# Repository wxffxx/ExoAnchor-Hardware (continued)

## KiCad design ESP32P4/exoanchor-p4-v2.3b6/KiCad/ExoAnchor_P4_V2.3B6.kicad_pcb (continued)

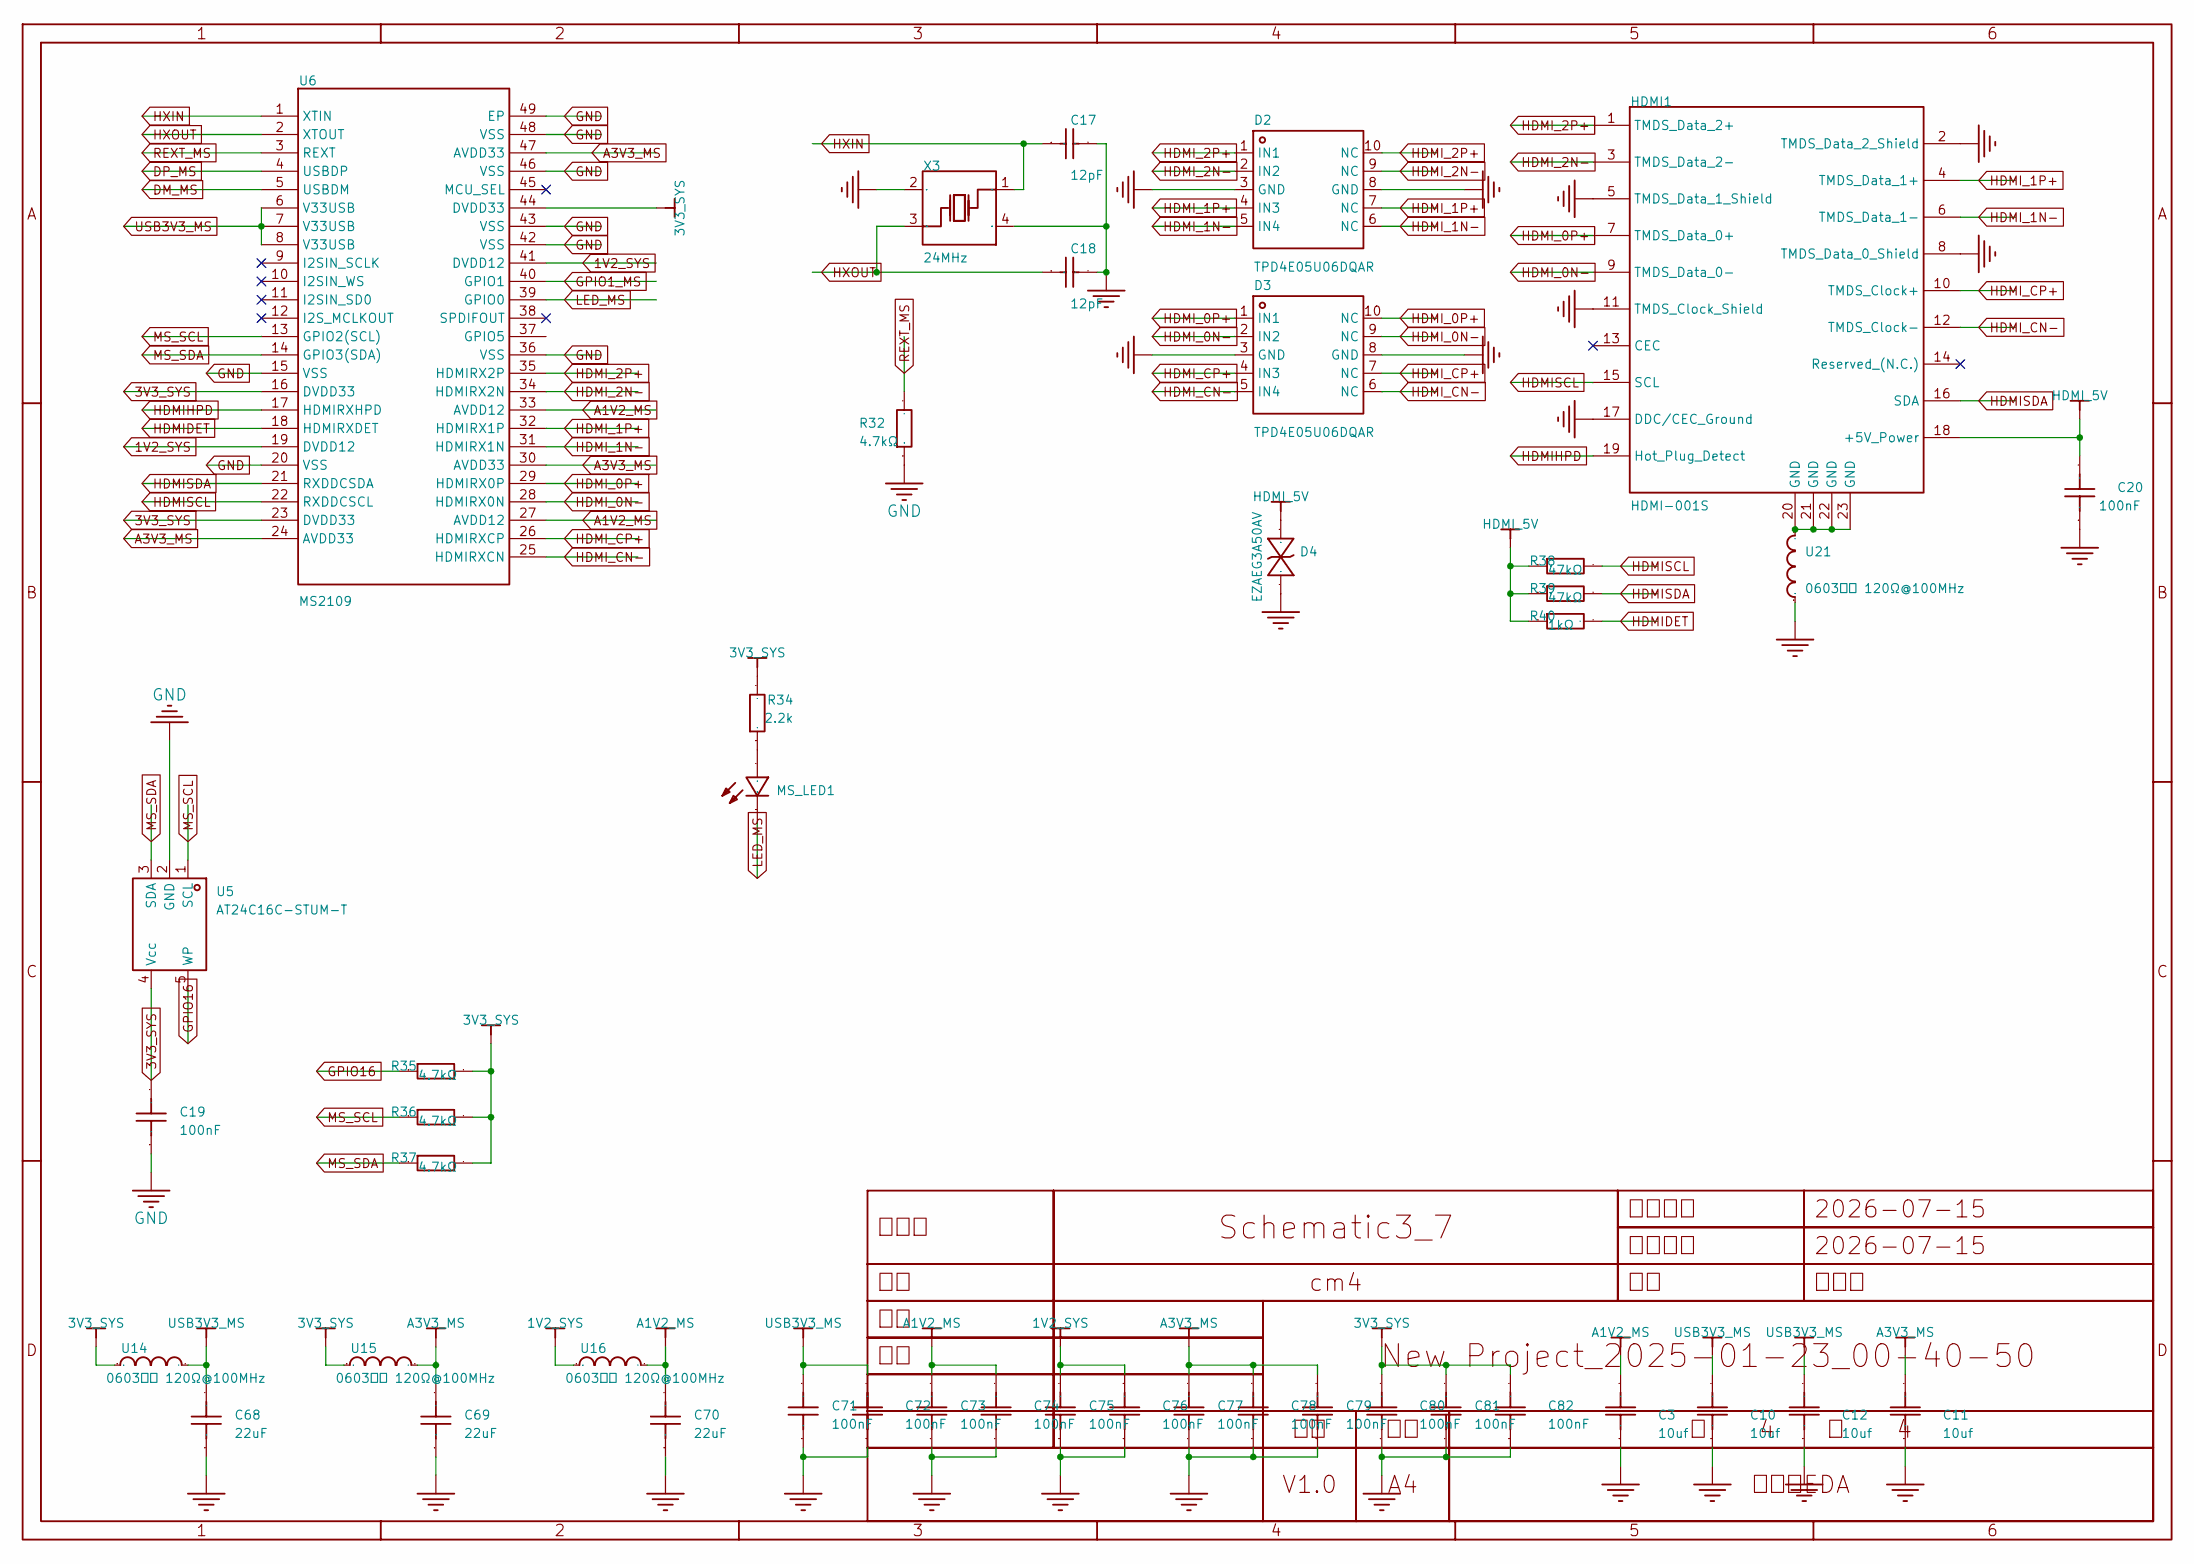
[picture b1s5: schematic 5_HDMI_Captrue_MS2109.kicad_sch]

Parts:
C3, C10, C11, C12: 10uf; C0603__a4480e4e; Tolerance ±10%; Voltage Rated 50V; Manufacturer Part CL10A105KB8NNNC; LCSC Part Name 1uF ±10% 50V
C17, C18: 12pF; C0402__aba8f707; Tolerance ±5%; Voltage Rating 50V; Manufacturer Part 0402CG120J500NT; LCSC Part Name 12pF ±5% 50V
C19, C20: 100nF; C0603__62af29ea; Tolerance ±10%; Voltage Rated 50V; Manufacturer Part CC0603KRX7R9BB104; LCSC Part Name 100nF ±10% 50V
C68, C69, C70: 22uF; C0805__eb27e37a; Tolerance ±20%; Voltage Rating 25V; Manufacturer Part CGA0805X5R226M250MT; LCSC Part Name 22uF ±20% 25V
C71, C72, C73, C74, C75, C76, C77, C78, C79, C80, C81, C82: 100nF; C0402 去耦电容__92f207f8; Tolerance ±10%; Voltage Rating 16V; Manufacturer Part CL05B104KO5NNNC; LCSC Part Name 100nF ±10% 16V
D2, D3: TPD4E05U06DQAR; USON-10_L2.5-W1.0-P0.50-BL__5b0cdc5b; Manufacturer Part TPD4E05U06DQAR; LCSC Part Name 单向ESD
D4: EZAEG3A50AV; D0603-BI__29d920bd; Manufacturer Part EZAEG3A50AV; LCSC Part Name EZAEG3A50AV
HDMI1: HDMI-001S; HDMI-SMD_HDMI-001S__cd4ec1f9; Manufacturer Part HDMI-001S; LCSC Part Name HDMI-001S
MS_LED1: LED0603-RD_RED__01c91157; Manufacturer Part NCD0603R1; LCSC Part Name NCD0603R1
R32: 4.7kΩ; R0402__b4a31b25; Tolerance ±1%; Voltage-Supply(Max) 50V; Manufacturer Part RC0402FR-074K7L; LCSC Part Name 厚膜电阻 4.7kΩ ±1% 62.5mW
R34: 2.2k; R0603__52b39882; Overload Voltage (Max) 75V; Tolerance ±1%; Manufacturer Part 0603WAF1001T5E; LCSC Part Name 1kΩ ±1% 100mW 厚膜电阻
R35, R36, R37: 4.7kΩ; R0603__601aad73; Tolerance ±1%; Manufacturer Part 0603WAF4701T5E; LCSC Part Name 4.7kΩ ±1% 100mW 厚膜电阻
R38, R39: 47kΩ; R0603__601aad73; Overload Voltage (Max) 75V; Tolerance ±1%; Manufacturer Part 0603WAF4701T5E; LCSC Part Name 4.7kΩ ±1% 100mW 厚膜电阻
R40: 1kΩ; R0603__52b39882; Overload Voltage (Max) 75V; Tolerance ±1%; Manufacturer Part 0603WAF1001T5E; LCSC Part Name 1kΩ ±1% 100mW 厚膜电阻
U5: AT24C16C-STUM-T; SOT-23-5_L2.9-W1.6-P0.95-LS2.8-BL__13f3e689; Manufacturer Part AT24C16C-STUM-T; LCSC Part Name 兼容I²C（两线制）的16 Kbit串行EEPROM
U6: MS2109; QFN-48_L7.0-W7.0-P0.50-TL-EP4.1__b8ae6dac
U14: L0603__0fd5099d; Manufacturer Part BLM18PG121SN1D; LCSC Part Name 0603磁珠 120Ω@100MHz
U15, U16, U21: BLM18PG121SN1D; L0603__0fd5099d; Current Rating 2A; Tolerance ±25%; Manufacturer Part BLM18PG121SN1D; LCSC Part Name 0603磁珠 120Ω@100MHz
X3: 24MHz; CRYSTAL-SMD_4P-L3.2-W2.5-BL__9c9dbee8; Manufacturer Part X322524MOB4SI; LCSC Part Name YSX321SL 24MHZ 4P 3225 12PF ±10PPM -40~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

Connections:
1V2_SYS: C75.2, C76.2, U6.19 (DVDD12), U6.41 (DVDD12), U16.1; also elsewhere on the board
3V3_SYS: C19.2, C80.2, C81.2, C82.2, R34.2, R35.2, R36.2, R37.2, U5.4 (Vcc), U6.16 (DVDD33), U6.23 (DVDD33), U6.44 (DVDD33), U14.1, U15.1; also elsewhere on the board
$5N3531: MS_LED1.2 (A), R34.1
$5N70958: HDMI1.20 (GND), HDMI1.21 (GND), HDMI1.22 (GND), HDMI1.23 (GND), U21.2
A1V2_MS: C3.2, C70.2, C73.2, C74.2, U6.27 (AVDD12), U6.33 (AVDD12), U16.2
A3V3_MS: C11.2, C69.2, C77.2, C78.2, C79.2, U6.24 (AVDD33), U6.30 (AVDD33), U6.47 (AVDD33), U15.2
DM_MS: U6.5 (USBDM); also elsewhere on the board
DP_MS: U6.4 (USBDP); also elsewhere on the board
GND: C3.1, C10.1, C11.1, C12.1, C17.2, C18.2, C19.1, C20.1, C68.1, C69.1, C70.1, C71.1, C72.1, C73.1, C74.1, C75.1, C76.1, C77.1, C78.1, C79.1, C80.1, C81.1, C82.1, D2.3 (GND), D2.8 (GND), D3.3 (GND), D3.8 (GND), D4.1 (K), HDMI1.2 (TMDS_Data_2_Shield), HDMI1.5 (TMDS_Data_1_Shield), HDMI1.8 (TMDS_Data_0_Shield), HDMI1.11 (TMDS_Clock_Shield), HDMI1.17 (DDC/CEC_Ground), R32.1, U5.2 (GND), U6.15 (VSS), U6.20 (VSS), U6.36 (VSS), U6.42 (VSS), U6.43 (VSS), U6.46 (VSS), U6.48 (VSS), U6.49 (EP), U21.1, X3.2 (GND), X3.4 (GND); also elsewhere on the board
GPIO1_MS: U6.40 (GPIO1)
GPIO16: R35.1, U5.5 (WP); also elsewhere on the board
HDMIDET: R40.2, U6.18 (HDMIRXDET)
HDMIHPD: HDMI1.19 (Hot_Plug_Detect), U6.17 (HDMIRXHPD)
HDMISCL: HDMI1.15 (SCL), R38.2, U6.22 (RXDDCSCL)
HDMISDA: HDMI1.16 (SDA), R39.2, U6.21 (RXDDCSDA)
HDMI_0N-: D3.2 (IN2), D3.9 (NC), HDMI1.9 (TMDS_Data_0-), U6.28 (HDMIRX0N)
HDMI_0P+: D3.1 (IN1), D3.10 (NC), HDMI1.7 (TMDS_Data_0+), U6.29 (HDMIRX0P)
HDMI_1N-: D2.5 (IN4), D2.6 (NC), HDMI1.6 (TMDS_Data_1-), U6.31 (HDMIRX1N)
HDMI_1P+: D2.4 (IN3), D2.7 (NC), HDMI1.4 (TMDS_Data_1+), U6.32 (HDMIRX1P)
HDMI_2N-: D2.2 (IN2), D2.9 (NC), HDMI1.3 (TMDS_Data_2-), U6.34 (HDMIRX2N)
HDMI_2P+: D2.1 (IN1), D2.10 (NC), HDMI1.1 (TMDS_Data_2+), U6.35 (HDMIRX2P)
HDMI_5V: C20.2, D4.2 (A), HDMI1.18 (+5V_Power), R38.1, R39.1, R40.1
HDMI_CN-: D3.5 (IN4), D3.6 (NC), HDMI1.12 (TMDS_Clock-), U6.25 (HDMIRXCN)
HDMI_CP+: D3.4 (IN3), D3.7 (NC), HDMI1.10 (TMDS_Clock+), U6.26 (HDMIRXCP)
HXIN: C17.1, U6.1 (XTIN), X3.1 (OSC1)
HXOUT: C18.1, U6.2 (XTOUT), X3.3 (OSC2)
LED_MS: MS_LED1.1 (K), U6.39 (GPIO0)
MS_SCL: R36.1, U5.1 (SCL), U6.13 (GPIO2(SCL)); also elsewhere on the board
MS_SDA: R37.1, U5.3 (SDA), U6.14 (GPIO3(SDA)); also elsewhere on the board
REXT_MS: R32.2, U6.3 (REXT)
USB3V3_MS: C10.2, C12.2, C68.2, C71.2, C72.2, U6.6 (V33USB), U6.7 (V33USB), U6.8 (V33USB), U14.2

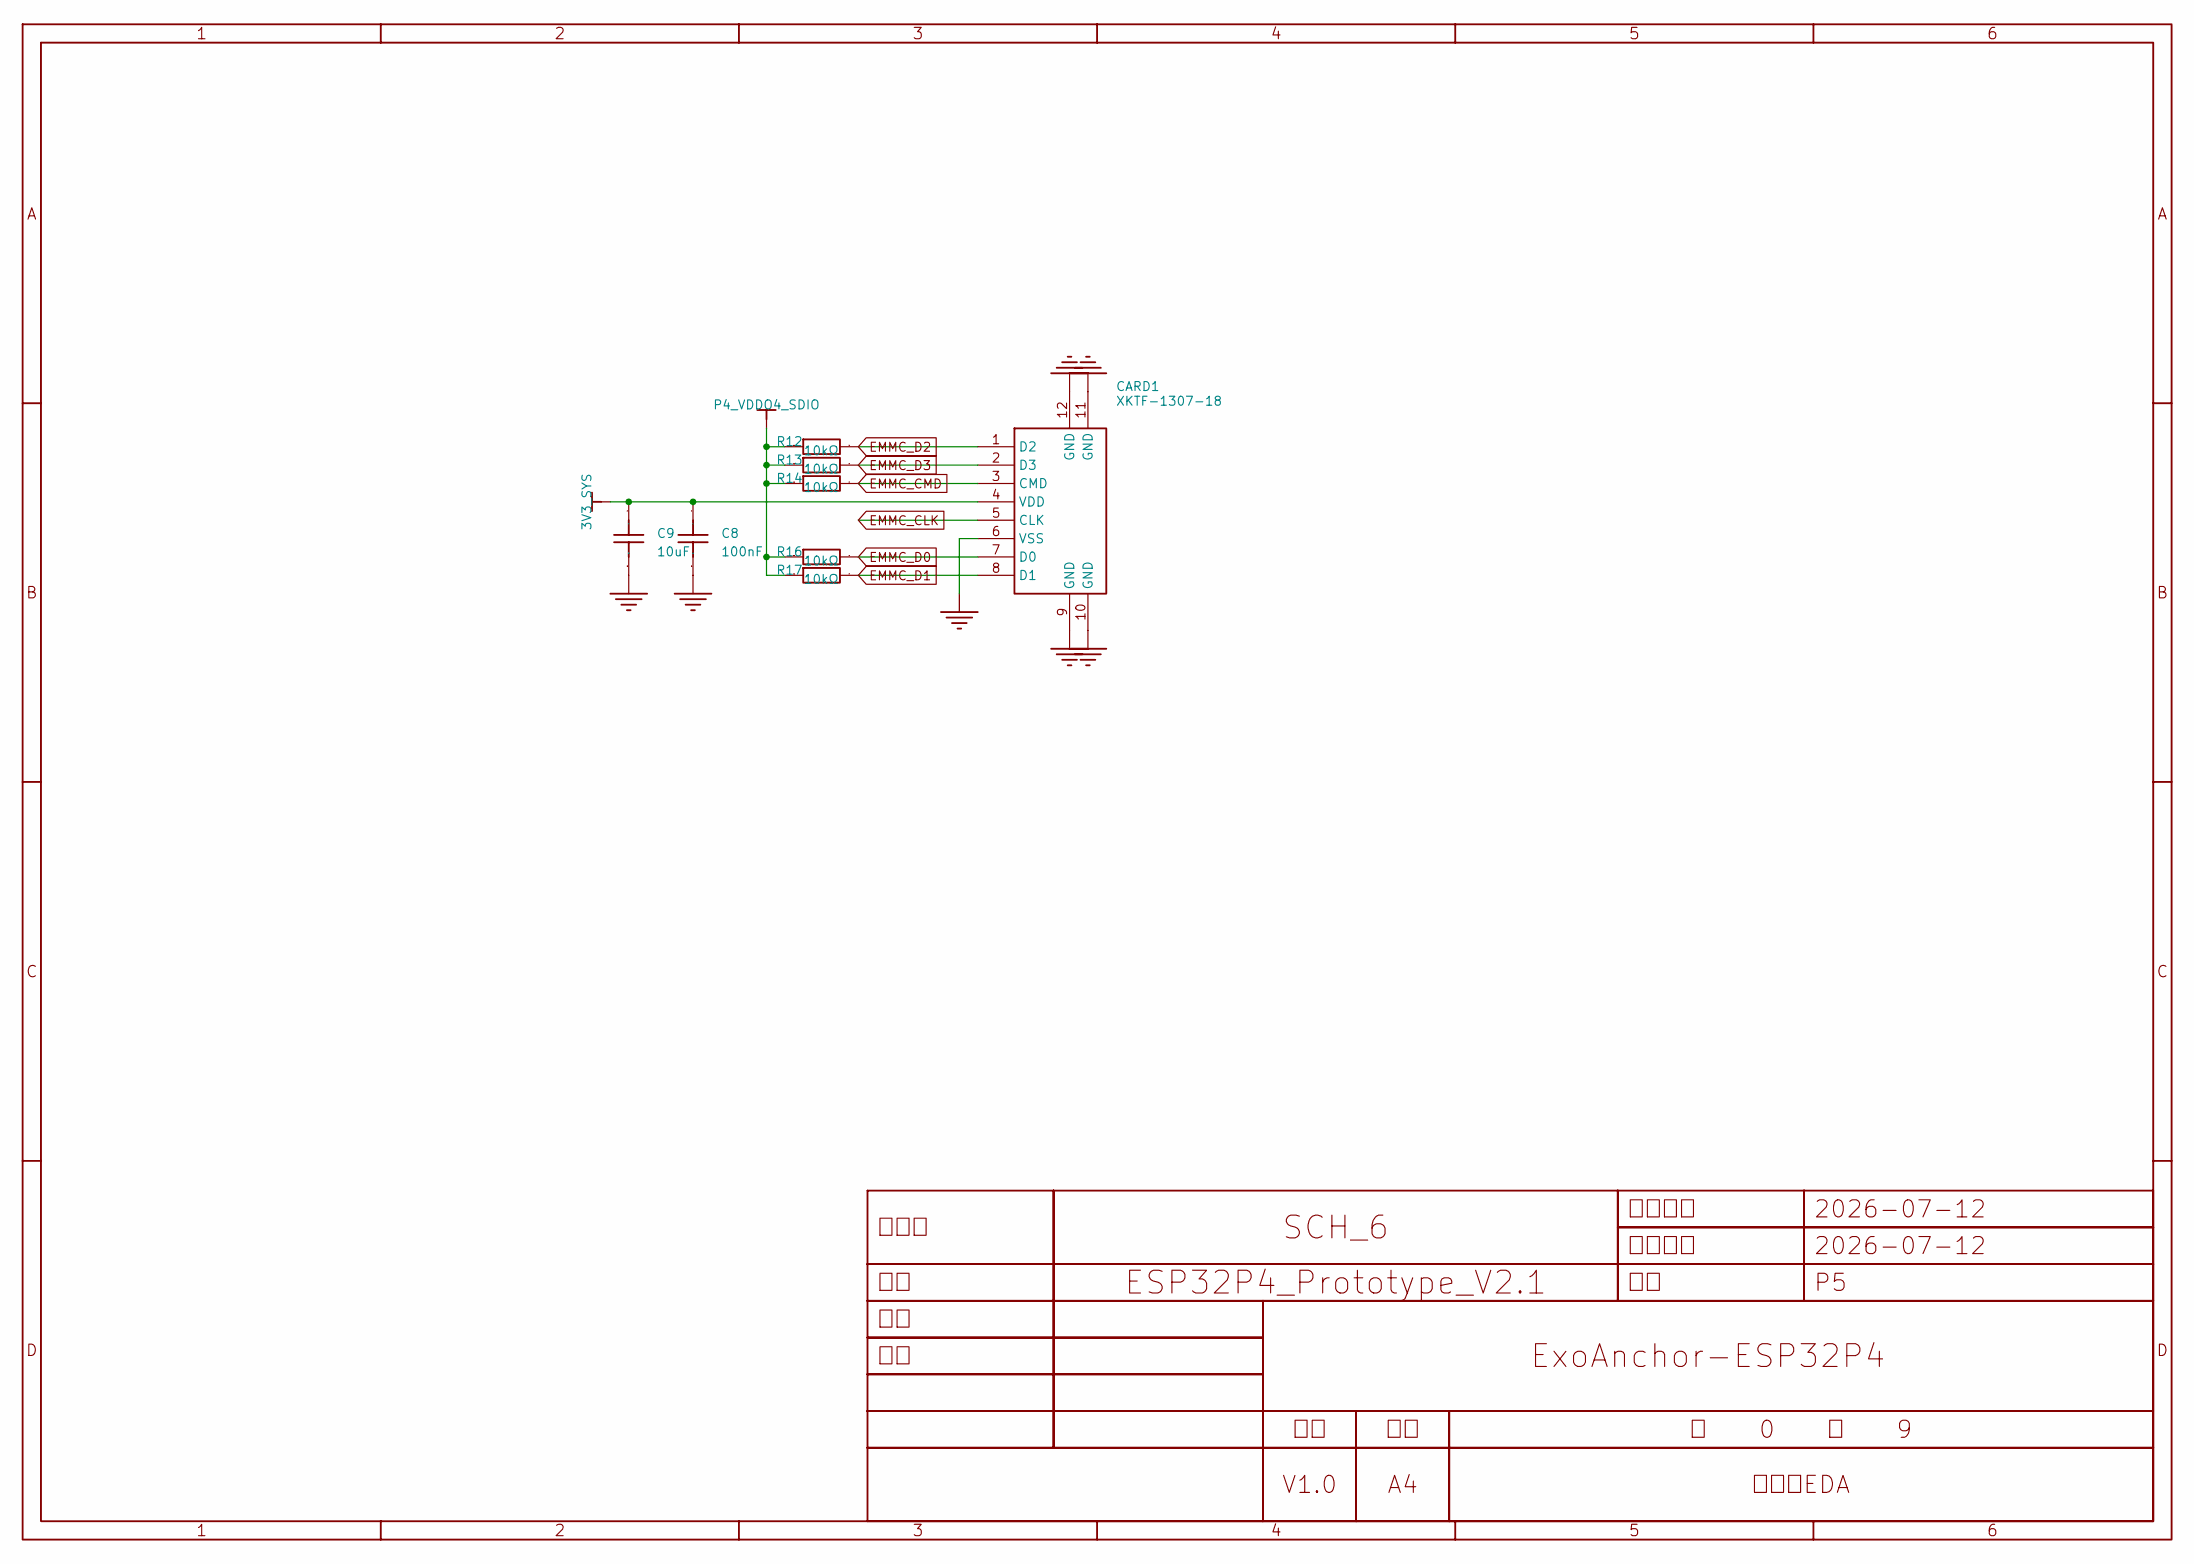
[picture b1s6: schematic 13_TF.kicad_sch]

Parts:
C8: 100nF; C0603__a4480e4e; Tolerance ±10%; Voltage Rating 16V; Manufacturer Part CL05B104KO5NNNC; LCSC Part Name 100nF ±10% 16V
C9: 10uF; C0603__a4480e4e; Tolerance ±20%; Voltage Rating 16V; Manufacturer Part CGA0603X5R106M160JT; LCSC Part Name 10uF ±20% 16V
CARD1: XKTF-1307-18; TF-SMD_XKTF-1307-18__7bd28ea8; Manufacturer Part XKTF-1307-18; LCSC Part Name 翻盖式 MicroSD卡(TF卡) 卡座
R12, R13, R14, R16, R17: 10kΩ; R0603__0f1821c5; Manufacturer Part FRC0402F1002TS; LCSC Part Name 10kΩ ±1% 62.5mW 厚膜电阻

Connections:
3V3_SYS: C8.2, C9.2, CARD1.4 (VDD); also elsewhere on the board
EMMC_CLK: CARD1.5 (CLK); also elsewhere on the board
EMMC_CMD: CARD1.3 (CMD), R14.2; also elsewhere on the board
EMMC_D0: CARD1.7 (D0), R16.2; also elsewhere on the board
EMMC_D1: CARD1.8 (D1), R17.2; also elsewhere on the board
EMMC_D2: CARD1.1 (D2), R12.2; also elsewhere on the board
EMMC_D3: CARD1.2 (D3), R13.2; also elsewhere on the board
GND: C8.1, C9.1, CARD1.6 (VSS), CARD1.9 (GND), CARD1.10 (GND), CARD1.11 (GND), CARD1.12 (GND); also elsewhere on the board
P4_VDDO4_SDIO: R12.1, R13.1, R14.1, R16.1, R17.1; also elsewhere on the board

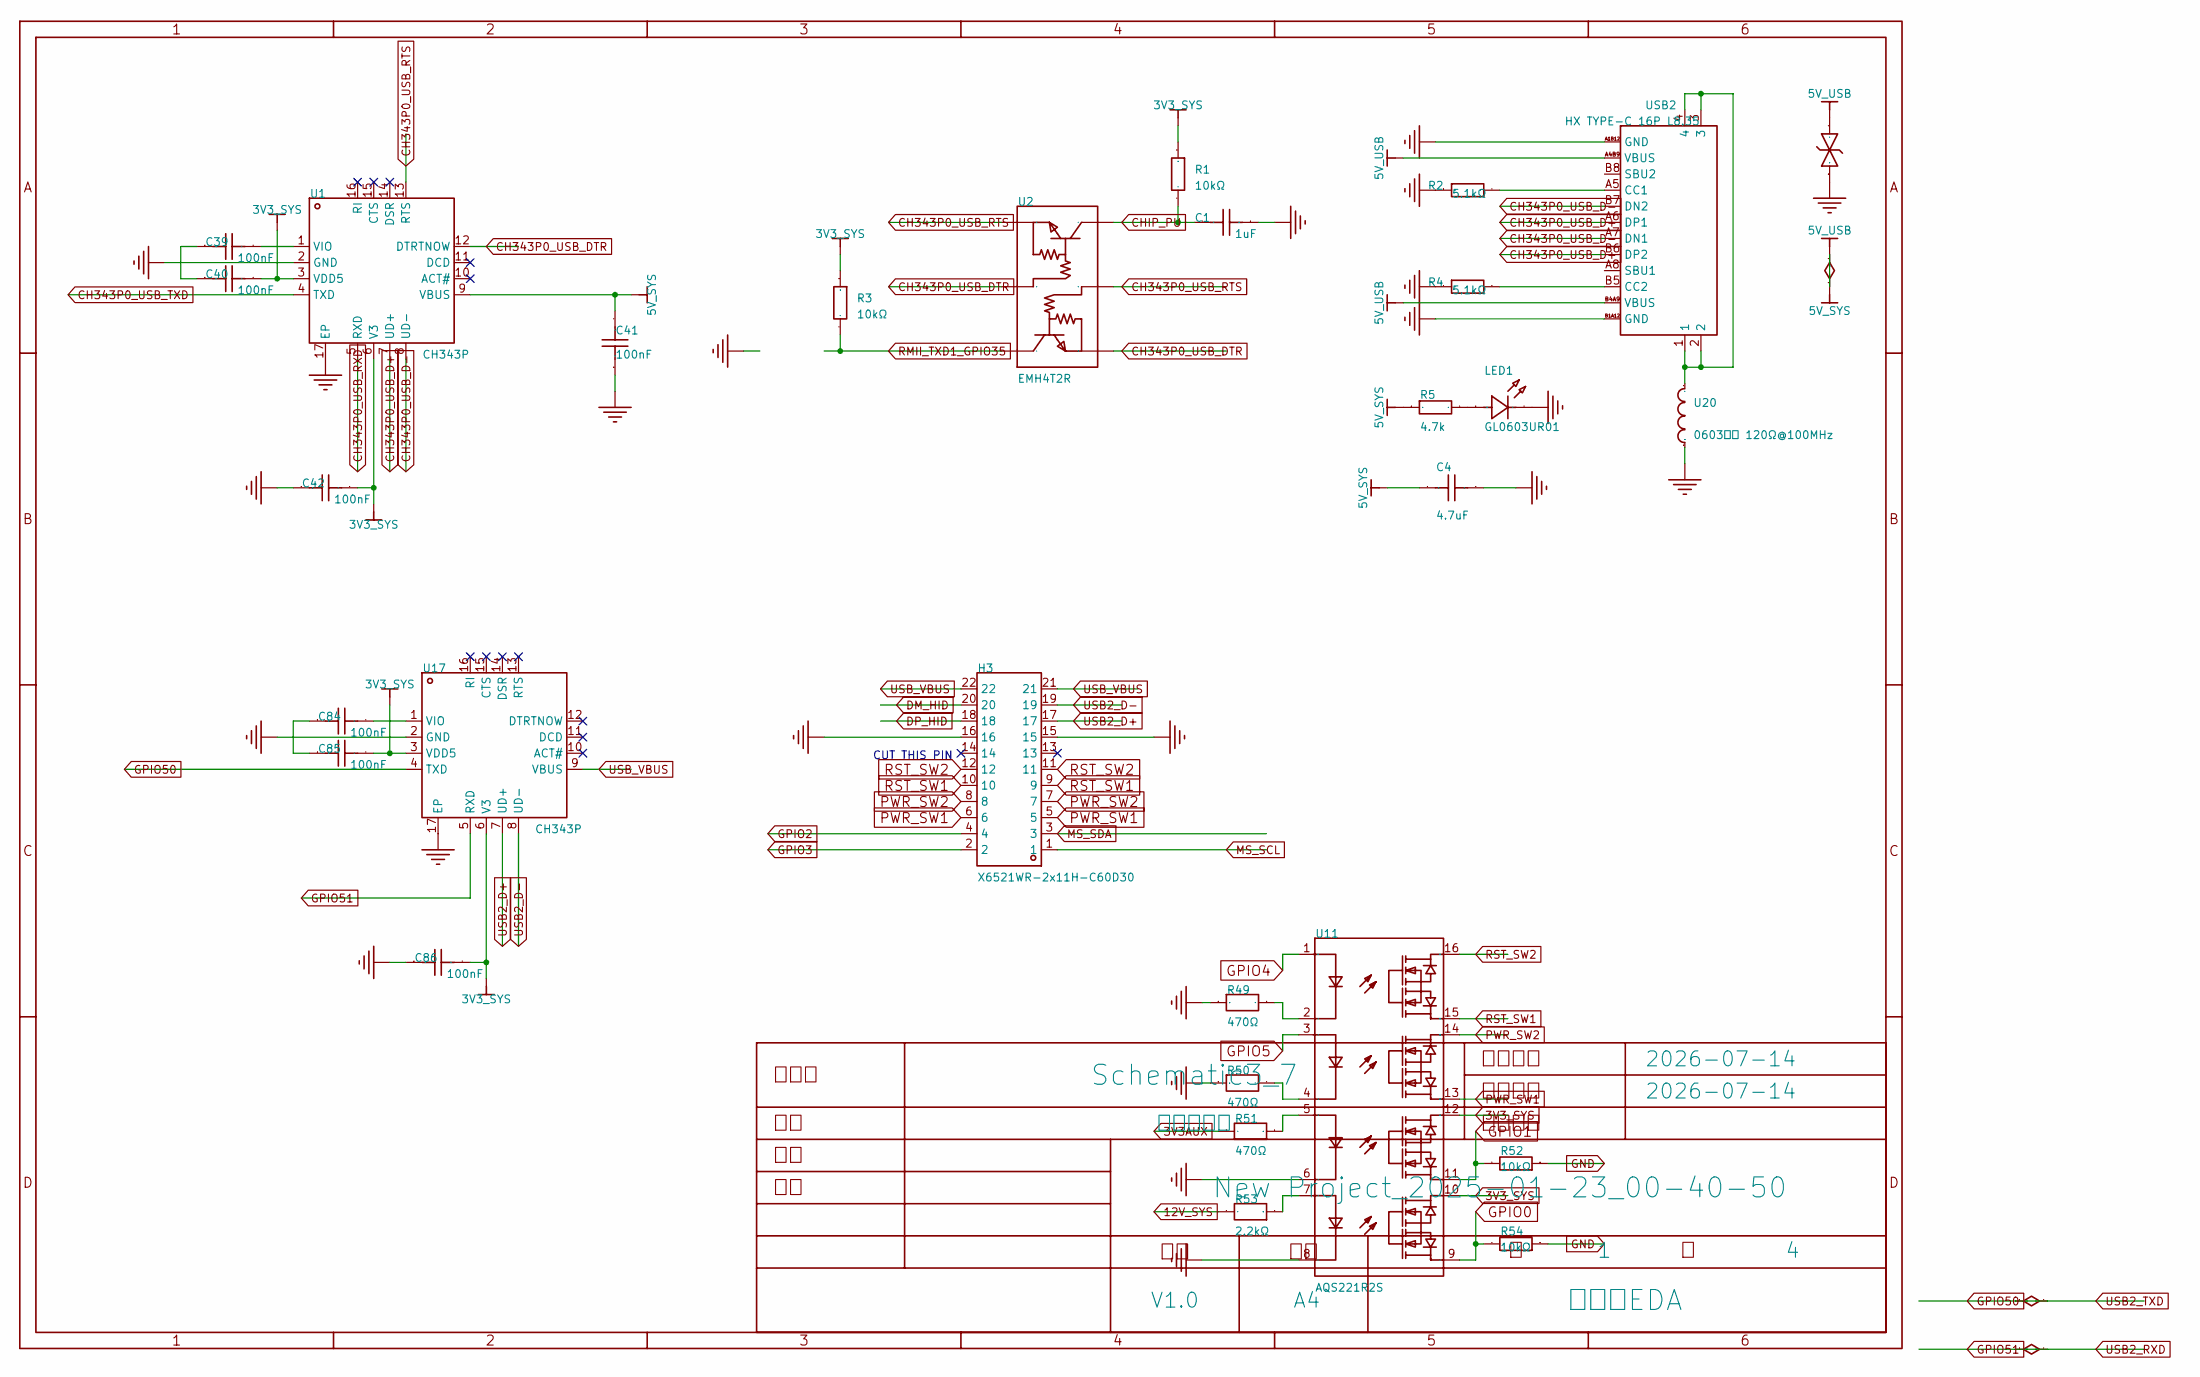
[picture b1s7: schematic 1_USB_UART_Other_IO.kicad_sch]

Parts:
C1: 1uF; C0402__aba8f707; Tolerance ±10%; Voltage Rating 25V; Manufacturer Part CL05A105KA5NQNC; LCSC Part Name 1uF ±10% 25V
C4: 4.7uF; C0805__eb27e37a; Tolerance ±20%; Voltage Rating 25V; Manufacturer Part CL21A226MAQNNNE; LCSC Part Name 22uF ±20% 25V
C39, C40, C41, C42, C84, C85, C86: 100nF; C0402 去耦电容__92f207f8; Tolerance ±10%; Voltage Rating 16V; Manufacturer Part CL05B104KO5NNNC; LCSC Part Name 100nF ±10% 16V
D1: SLPESD0603M05; D0603-BI__29d920bd; Clamping Voltage 40V; Manufacturer Part SLPESD0603M05; LCSC Part Name 双向ESD 5V截止
H3: X6521WR-2x11H-C60D30; HDR-TH_22P-P2.54-H-M-R2-C11-S2.54__330bd00a; Manufacturer Part X6521WR-2x11H-C60D30; LCSC Part Name 2x11P 间距:2.54mm 方针
LED1: GL0603UR01; LED0603-FD__402ba6a9; Voltage - Forward(Vf) 2.4V; Manufacturer Part GL0603UR01; LCSC Part Name 0603 红灯 高亮
R1, R3: 10kΩ; R0402__b4a31b25; Tolerance ±1%; Voltage-Supply(Max) 50V; Manufacturer Part 0402WGF1002TCE; LCSC Part Name 10kΩ ±1% 62.5mW 厚膜电阻
R2, R4: 5.1kΩ; R0402__b4a31b25; Tolerance ±5%; Voltage-Supply(Max) 50V; Manufacturer Part FRC0402J512 TS; LCSC Part Name 5.1kΩ ±5% 62.5mW 厚膜电阻
R5: 4.7k; R0402__b4a31b25; Tolerance ±1%; Voltage-Supply(Max) 50V; Manufacturer Part 0402WGF2201TCE; LCSC Part Name 2.2kΩ ±1% 62.5mW 厚膜电阻
R49, R50, R51: 470Ω; R0603__0f1821c5; Tolerance ±5%; Voltage-Supply(Max) 75V; Manufacturer Part FRC0603J471 TS; LCSC Part Name 470Ω ±5% 100mW 厚膜电阻
R52, R54: 10kΩ; R0603__601aad73; Tolerance ±1%; Voltage-Supply(Max) 75V; Manufacturer Part 0603WAF1002T5E; LCSC Part Name 厚膜电阻 10kΩ ±1% 100mW
R53: 2.2kΩ; R0603__0f1821c5; Tolerance ±1%; Voltage-Supply(Max) 75V; Manufacturer Part FRC0603F2201TS; LCSC Part Name 2.2kΩ ±1% 100mW 厚膜电阻
U1: CH343P; TQFN-16_L3.0-W3.0-P0.50-BL-EP1.7__72e19bbc; Manufacturer Part CH343P; LCSC Part Name CH343P
U2: EMH4T2R; SOT-563-6_L1.6-W1.2-P0.50-LS1.6-BL__0ee4edd2; Manufacturer Part EMH4T2R; LCSC Part Name 通用双数字晶体管
U11: AQS221R2S; SO-16_L10.3-W4.4-P1.27-LS7.0-BL__4ca11b91; Manufacturer Part AQS221R2S; LCSC Part Name AQS221R2S
U17: CH343P; TQFN-16_L3.0-W3.0-P0.50-BL-EP1.7__72e19bbc; Voltage - Supply 3.3V；5V; Manufacturer Part CH343P; LCSC Part Name CH343P
U20: BLM18PG121SN1D; L0603__0fd5099d; Current Rating 2A; Tolerance ±25%; Manufacturer Part BLM18PG121SN1D; LCSC Part Name 0603磁珠 120Ω@100MHz
USB2: HX TYPE-C 16P L8.35; USB-C-SMD_HX-TYPE-C-16P-L8.35__cf6aeb05; Manufacturer Part HX TYPE-C 16P L8.35; LCSC Part Name Type-C 母 卧贴

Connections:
3V3AUX: R51.2; also elsewhere on the board
3V3_SYS: C39.2, C40.2, C42.2, C84.2, C85.2, C86.2, R1.1, R3.1, U1.1 (VIO), U1.3 (VDD5), U1.6 (V3), U11.10, U11.12, U17.1 (VIO), U17.3 (VDD5), U17.6 (V3); also elsewhere on the board
12V_SYS: R53.2; also elsewhere on the board
$1N39290: LED1.1 (A), R5.2
$1N39352: R4.2, USB2.B5 (CC2)
$1N39354: R2.2, USB2.A5 (CC1)
$1N39473: U20.2, USB2.1, USB2.2, USB2.3, USB2.4
$1N39591: R51.1, U11.5
$1N39592: R53.1, U11.7
$1N39604: R50.2, U11.4
$1N39607: R49.2, U11.2
CH343P0_USB_D+: U1.7 (UD+), USB2.A6 (DP1), USB2.B6 (DP2)
CH343P0_USB_D-: U1.8 (UD-), USB2.A7 (DN1), USB2.B7 (DN2)
CH343P0_USB_DTR: U1.12 (DTRTNOW), U2.1 (E), U2.5 (B)
CH343P0_USB_RTS: U1.13 (RTS), U2.2 (B), U2.4 (E)
CH343P0_USB_RXD: U1.5 (RXD); also elsewhere on the board
CH343P0_USB_TXD: U1.4 (TXD); also elsewhere on the board
CHIP_PU: C1.2, R1.2, U2.3 (C); also elsewhere on the board
DM_HID: H3.20; also elsewhere on the board
DP_HID: H3.18; also elsewhere on the board
GND: C1.1, C4.2, C39.1, C40.1, C41.1, C42.1, C84.1, C85.1, C86.1, D1.1, H3.15, H3.16, LED1.2 (C), R2.1, R4.1, R49.1, R50.1, R52.1, R54.1, U1.2 (GND), U1.17 (EP), U11.6, U11.8, U17.2 (GND), U17.17 (EP), U20.1, USB2.A1B12 (GND), USB2.B1A12 (GND); also elsewhere on the board
GPIO0: R54.2, U11.9; also elsewhere on the board
GPIO1: R52.2, U11.11; also elsewhere on the board
GPIO2: H3.4; also elsewhere on the board
GPIO3: H3.2; also elsewhere on the board
GPIO4: U11.1; also elsewhere on the board
GPIO5: U11.3; also elsewhere on the board
MS_SCL: H3.1; also elsewhere on the board
MS_SDA: H3.3; also elsewhere on the board
PWR_SW1: H3.5, H3.6, U11.13
PWR_SW2: H3.7, H3.8, U11.14
RMII_TXD1_GPIO35: R3.2, U2.6 (C); also elsewhere on the board
RST_SW1: H3.9, H3.10, U11.15
RST_SW2: H3.11, H3.12, U11.16
USB2_D+: H3.17, U17.7 (UD+)
USB2_D-: H3.19, U17.8 (UD-)
USB_VBUS: H3.21, H3.22, U17.9 (VBUS)

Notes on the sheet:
CUT THIS PIN
